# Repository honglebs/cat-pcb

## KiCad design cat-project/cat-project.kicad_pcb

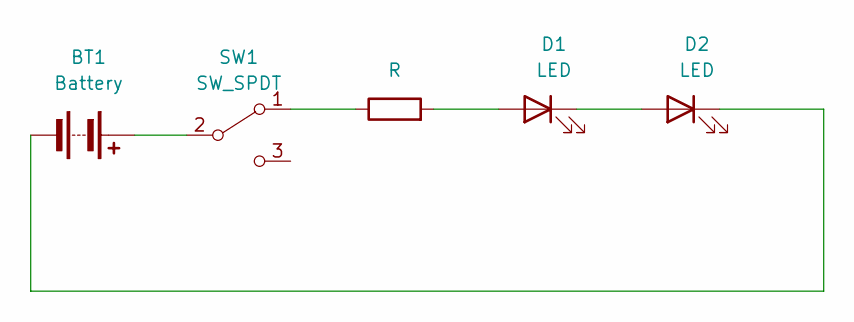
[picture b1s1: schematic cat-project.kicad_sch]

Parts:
BT1: Battery; BatteryHolder_Keystone_1058_1x2032
D1, D2: LED; LED_D3.0mm
R1: R; R_Axial_DIN0207_L6.3mm_D2.5mm_P10.16mm_Horizontal
SW1: SW_SPDT; SW_DIP_SPSTx01_Slide_6.7x4.1mm_W7.62mm_P2.54mm_LowProfile

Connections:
unnamed: BT1.1 (+), SW1.2 (B)
unnamed: BT1.2 (-), D2.1 (K)
unnamed: D1.2 (A), R1.2
unnamed: D1.1 (K), D2.2 (A)
unnamed: R1.1, SW1.1 (A)

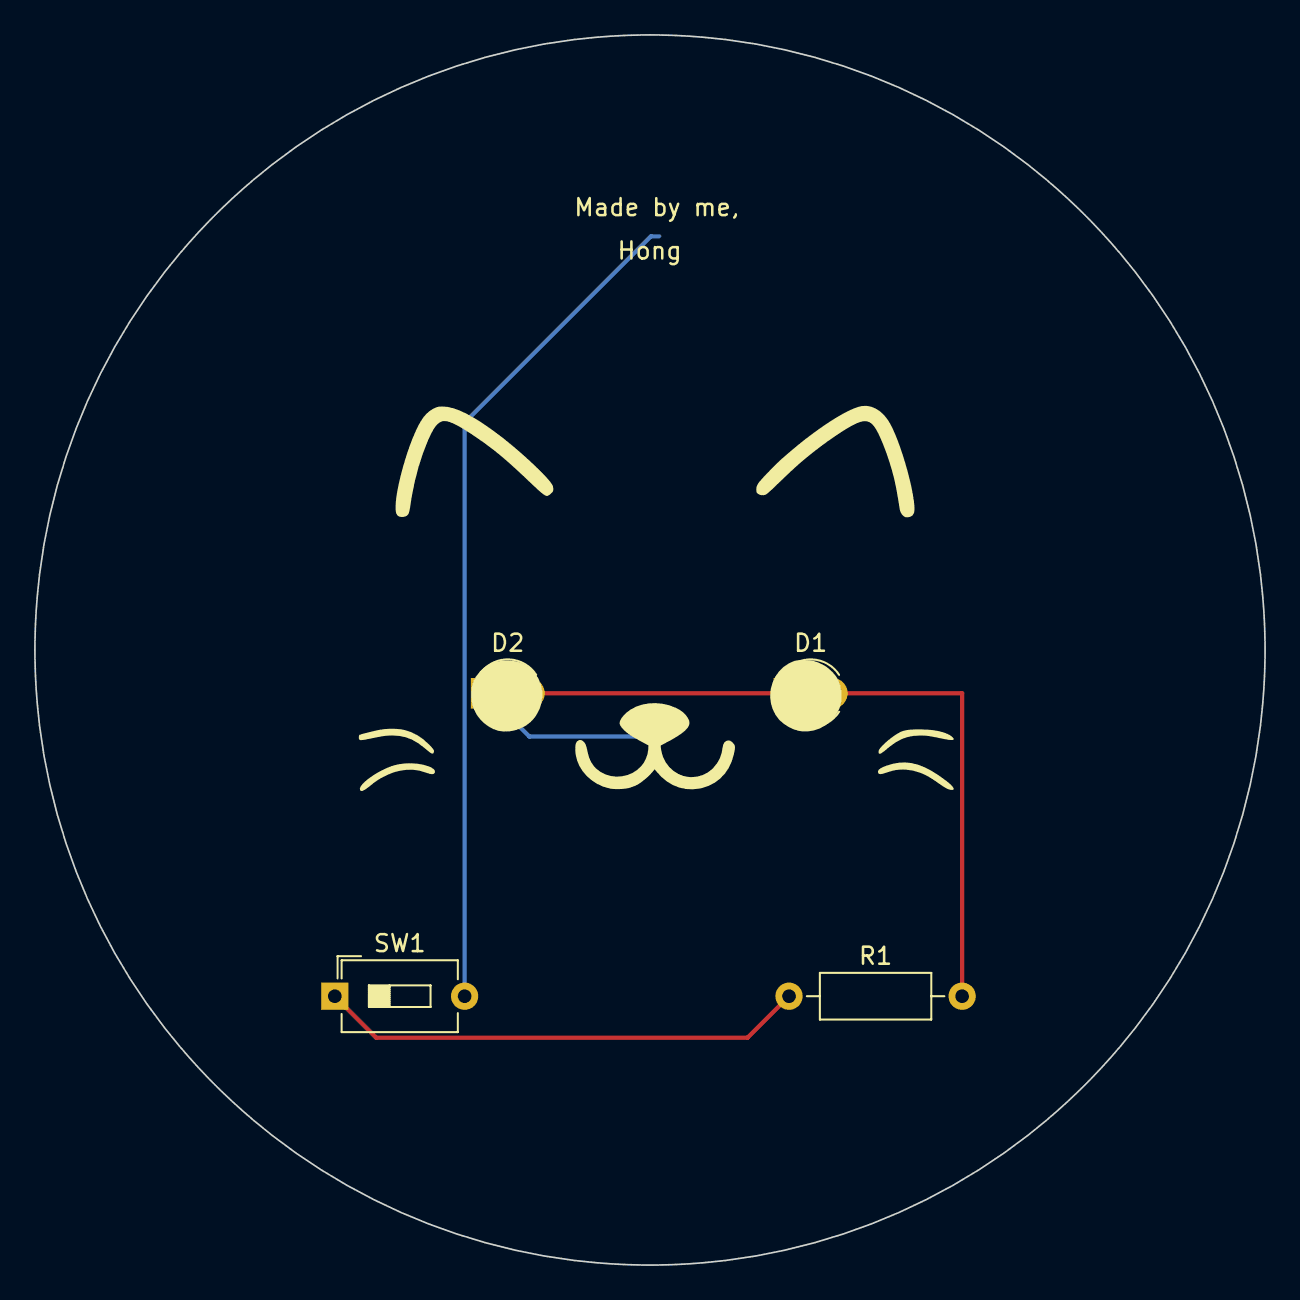
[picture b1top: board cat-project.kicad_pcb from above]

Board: 2 copper layers, 72.2 x 72.2 mm, 5 parts (1 on the bottom side), 5 nets.
